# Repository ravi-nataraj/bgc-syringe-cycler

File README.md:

# BGC Syringe Cycler

Ten-station pneumatic fatigue cycling fixture for balloon guide catheter inflation testing. A single 5/2 solenoid valve drives ten double-acting air cylinders in parallel, each actuating a 1 mL Merit Medical Medallion syringe. Pusher and mount spacing fixes the stroke to displace ~0.6 mL per cycle.

The cycling regime is adapted from ISO 10555-4:2023 Annex B (balloon
fatigue / repeated inflation). Annex B is written for dilatation
balloons and cycles to rated burst pressure; a balloon guide catheter is specified by recommended inflation volume rather than RBP, so the fixture cycles a fixed displaced volume instead. Annex B's default of 10 cycles is likewise adapted — the fixture defaults to 20 — which the standard permits where supported by risk assessment.

Cycle timing is configurable to accommodate different test fluids —
viscous media such as contrast refill the syringe more slowly than
saline or DI water. Timing and cycle count can be set from any device over WiFi, or the fixture can be run from a single button using its DI water / saline defaults (60s on, 10s off, 20 cycles).

---

## What it does

A run repeats one cycle: all ten cylinders extend, hold, retract, hold.
Defaults are 60 s extended, 10 s retracted, 20 cycles — about 23 minutes.

The cylinders are plumbed in parallel off two distribution manifolds, so
they move together. The controller switches a single valve coil, so
station count is a pneumatic change, not an electrical one.

---

## Running it

### From the button

Power the PCB from a 12 V DC supply (2.5 mm barrel jack, 1 A min).
Short-press the button on the control board to start. The run uses the
current settings and stops on its own. Defaults are 60 s extended,
10 s retracted, 20 cycles.

To abort mid-run, **press and hold the button for 1 second.** The valve
de-energizes immediately and the cylinders retract. A short press during
an active run does nothing, by design.

To change timing or cycle count, see the next section.

### From any device

1. Join the WiFi network **`walrus`**, password **`walrus123`**
2. Open a browser to **192.168.4.1** (add `http://` if the browser tries
to search instead of navigate).
3. Set extend time, retract time and cycle count, then **Save**
4. Press **Start run**

The page shows live status while the fixture runs: which cycle, whether
it is extended or retracted, and time remaining.

Settings lock while a run is in progress. Press **Stop and reset**, or
hold the board button, to unlock them.

Your phone will report "no internet connection" — expected, since the
board is its own access point. If your phone drops the network
automatically, tell it to stay connected when prompted.

The run continues if you disconnect. Reconnect any time to see live
status or stop the run.

### Status LED

| LED | Meaning |
|---|---|
| Off | Idle, waiting |
| Solid | Extended |
| Blinking | Retracted, between cycles |

### Defaults

Settings are held in RAM only. **Cutting power returns the fixture to
60 s / 10 s / 20 cycles**, so the next user always starts from a known
configuration. There is also a *Restore defaults* button on the web
page.

---

## Setting up the pneumatics

| Setting | Value |
|---|---|
| Supply pressure | 60 psi |
| Valve minimum | 44 psi — do not go below this |
| Valve maximum | 145 psi |
| Cylinder | 7/16" bore, 2" stroke |

Set the regulator to **60 psi**. The valve will not shift reliably below 44 psi, so watch the gauge during a ten-cylinder actuation and confirm it does not dip toward that floor. If it does, raise the supply pressure.

Stroke speed is set by the meter-out flow controls on the valve's two exhaust ports, not in firmware.

**Verify stroke before the first run.** The printed pusher bottoms
against the stationary mount, which fixes delivered volume at ~0.6 mL. Cycle once dry and confirm the pusher contacts the mount versus if plunger reaches the end of the barrel.

---

## Repository layout

```
bgc-syringe-cycler/
├── docs/
│   ├── images/                          photos and reference images
│   ├── design-notes.md                  reasoning behind major decisions
│   └── firmware-setup.md                Arduino IDE and board setup
├── firmware/
│   └── syringe_cycler_wifi_volatile.ino
├── hardware/
│   ├── gerbers/                         fabrication output, as ordered
│   ├── images/                          board renders and layout
│   ├── kicad/                           schematic, PCB, dependent libraries
│   └── snoid-swt-BOM.csv                control board bill of materials
├── mechanical/
│   ├── step/                            neutral CAD exports
│   ├── sw-pack-n-go/                    SolidWorks source
│   ├── bgc-inflation-fatigue-assy.pdf   assembly drawing
│   └── mechanical-BOM.csv               fixture bill of materials
├── .gitignore
├── LICENSE
└── README.md
```

Hardware, firmware, and mechanical source for the fixture, plus the
build and setup documentation.

---

## Control board

Custom two-layer PCB ordered from JLPCB. A XIAO ESP32-C3 sits in a socket and switches the 12 V valve coil through a logic-level MOSFET.

| Function | Part |
|---|---|
| MCU | Seeed XIAO ESP32-C3, socketed |
| Valve switch | IRLZ44N, low-side |
| Flyback | 1N4007 across the coil |
| Reverse protection | IRF9540N P-channel, high-side |
| Overcurrent | 0.9 A resettable polyfuse |
| 5 V supply | OKI-78SR-5, switching, TO-220 pinout |
| Input | 12 V, 5.5 × 2.5 mm barrel jack, centre positive |

Seven test points are brought out: 12VIN, 12V, 5V, 3V3, GND, GATE and
DRAIN. See `docs/troubleshooting.md` for what to expect at each.

---

## Building the firmware

Arduino IDE with the ESP32 board package installed.

| Setting | Value |
|---|---|
| Board | XIAO_ESP32C3 |
| USB CDC On Boot | **Enabled** — required, or Serial does nothing |
| Upload spesed | 921600 |
| Serial monitor | 115200 |

Program the XIAO out of its socket, plugged straight into USB.

Serial commands also work: `E60` extend seconds, `R10` retract seconds,
`C20` cycle count, `S` start, `X` stop, `D` restore defaults.

---

## Bringing up a new board

Work through these in order.

1. **Unpowered.** Check continuity between +12 V and GND — should be
   open. A beep means a short; find it before applying power.
2. **12 V in, XIAO out of its socket.** Meter TP4 for 5.00 V.
3. **Power down, insert the XIAO, power up.** The serial banner should print and the LED should respond to the button.
4. **Connect the coil.** Listen for two clicks per cycle, one on and
   one off. No air yet.
5. **Connect air** at 60 psi and run three cycles before committing to a full run.

---

## Known limitations

- **No independent station control.** All ten cylinders actuate together from a shared supply. A single station cannot be paused, removed, or run on a different profile mid-test.
- **Ten units per run.** Each run tests ten units (one lot). A 29-unit attribute sample therefore takes three runs (10/10/9), with one station left empty on the final run.
- **Open-loop timing.** Stroke timing is fixed in firmware. The fixture does not confirm that each cylinder reached its end of travel, so a stalled or short-stroked station will not be flagged. Verify stroke by visual inspection.
- **Aggressive return stroke.** The return stroke can retract the plunger fast enough to pull the white plunger rod out of the plunger stopper. Inspect plunger assemblies periodically during long cycle runs.
- **Limited network security.** The WiFi access point is protected only by a shared password and has no user authentication or access logging. It is intended as a DV bench fixture, not a secured or validated instrument.

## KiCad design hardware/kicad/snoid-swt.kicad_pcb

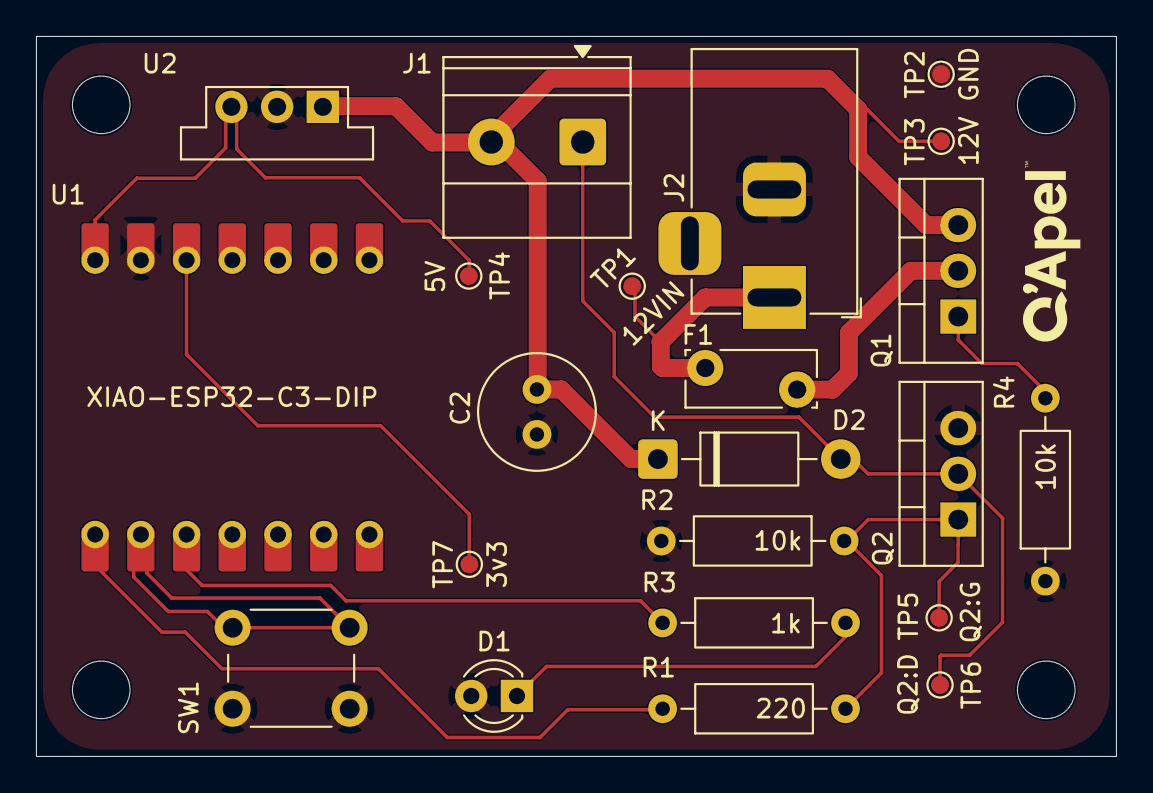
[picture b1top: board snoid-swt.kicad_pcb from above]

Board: 2 copper layers, 60.0 x 40.0 mm, 26 parts (0 on the bottom side), 13 nets.

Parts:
C2: 100 uF; C_Radial_D6.3mm_H11.0mm_P2.50mm
D1: LED; LED_D3.0mm
D2: 1N4007; D_DO-41_SOD81_P10.16mm_Horizontal
F1: Polyfuse; Fuse_Bourns_MF-RG300
J1: Screw_Terminal_01x02; TerminalBlock_Phoenix_MKDS-1,5-2-5.08_1x02_P5.08mm_Horizont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
J2: Barrel_Jack; BarrelJack_Horizontal
Q1: IRF9540N; TO-220-3_Vertical
Q2: IRLZ44N; TO-220-3_Vertical
R1: 220; R_Axial_DIN0207_L6.3mm_D2.5mm_P10.16mm_Horizontal
R2, R4: 10k; R_Axial_DIN0207_L6.3mm_D2.5mm_P10.16mm_Horizontal
R3: 1k; R_Axial_DIN0207_L6.3mm_D2.5mm_P10.16mm_Horizontal
SW1: SW_Push; SW_PUSH_6mm
TP1: 12VIN; TestPoint_Pad_D1.0mm
TP2: GND; TestPoint_Pad_D1.0mm
TP3: 12V; TestPoint_Pad_D1.0mm
TP4: 5V; TestPoint_Pad_D1.0mm
TP5: Q2:G; TestPoint_Pad_D1.0mm
TP6: Q2:D; TestPoint_Pad_D1.0mm
TP7: 3v3; TestPoint_Pad_D1.0mm
U1: XIAO-ESP32-C3-DIP
U2: OKI-78SR-5; Converter_DCDC_Murata_OKI-78SR_Vertical
m3-hole, m3-hole#2, m3-hole#3, m3-hole#4: MountingHole_3.2mm_M3

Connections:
+12V: C2.1, D2.1 (K), J1.2, Q1.3 (S), TP3.1 (1_1), U2.1 (IN)
GND: C2.2, D1.2 (A), J2.2, Q2.3 (S), R2.1, R4.1, SW1.1, TP2.1 (1_1), U1.13 (GND), U2.2 (GND)
unnamed: D1.1 (K), R3.2
unnamed: D2.2 (A), J1.1, Q2.2 (D), TP6.1 (1_1)
unnamed: F1.2, J2.1, TP1.1 (1_1)
unnamed: F1.1, Q1.2 (D)
unnamed: Q1.1 (G), R4.2
unnamed: Q2.1 (G), R1.1, R2.2, TP5.1 (1_1)
unnamed: TP7.1 (1_1), U1.12 (3V3_OUT)
unnamed: R1.2, U1.1 (D0)
unnamed: SW1.2, U1.2 (D1)
unnamed: R3.1, U1.3 (D2)
unnamed: TP4.1 (1_1), U1.14 (VBUS), U2.3 (OUT)
